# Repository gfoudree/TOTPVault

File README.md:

# TOTPVault

TOTPVault is a secure hardware vault for storing TOTP codes for two-factor authentication. It is compatible with websites and applications which support authenticators such as Google Authenticator or Authy.

TOTPVault uses an RISC-V ESP32-C3 microcontroller to perform cryptographic operations and storage/generation of TOTP codes with a separate chip to run an isolated USB stack.

## Demo

## Features

- Support for up to 64 credentials
- Cross platform, no drivers needed for Linux/MacOS
- Open source firmware, software, and hardware!

### Security Features (summary)
- TOTP secrets stored with AES256, decryption key derived from vault password via PBKDF2
- Trusted firmware via secure boot with attestation available
- ESP32-C3 HW RNG used for cryptographic operations
- USB stack isolated to separate chip to minimize attack surface
- Hardware locked down (JTAG disabled, eFuses set, etc)

# System Architecture
[System Architecture](https://gfoudree.github.io/TOTPVault/system-design/)

## Installation

First, clone the repository and build the `totpvault-cli` tool and build it:

```bash
git clone https://github.com/gfoudree/totpvault
cd totpvault/totpvault-cli
cargo build -r
```

The CLI program will be located at: `target/release/totpvault-cli`
## Documentation

[Documentation](https://gfoudree.github.io/TOTPVault/)

# FAQ

#### Why choose ESP32-C3 for the microcontroller?
The ESP32 chips have strong hardware security features such as HWRNG, encryption/hashing support, secure boot, and encrypted flash.

Other chips have some or all of these features, however the ESP32-C3 is [PSA-L1 certified](https://products.psacertified.org/products/esp32-c3-series/certificates#security-level-1), has good support for Rust firmware, and is affordable.

#### The ESP32 has Wifi/Bluetooth, does this device use either?
No, there is no antenna on the board and the Wifi/Bluetooth stack is disabled in the firmware.

#### If somebody steals my device, can they generate TOTP codes for my accounts?
No, as long as your password is strong they cannot unlock the vault and generate codes.

## Authors

- [@gfoudree](https://www.github.com/gfoudree)

## License

[GNU GPLv3](https://choosealicense.com/licenses/gpl-3.0/)

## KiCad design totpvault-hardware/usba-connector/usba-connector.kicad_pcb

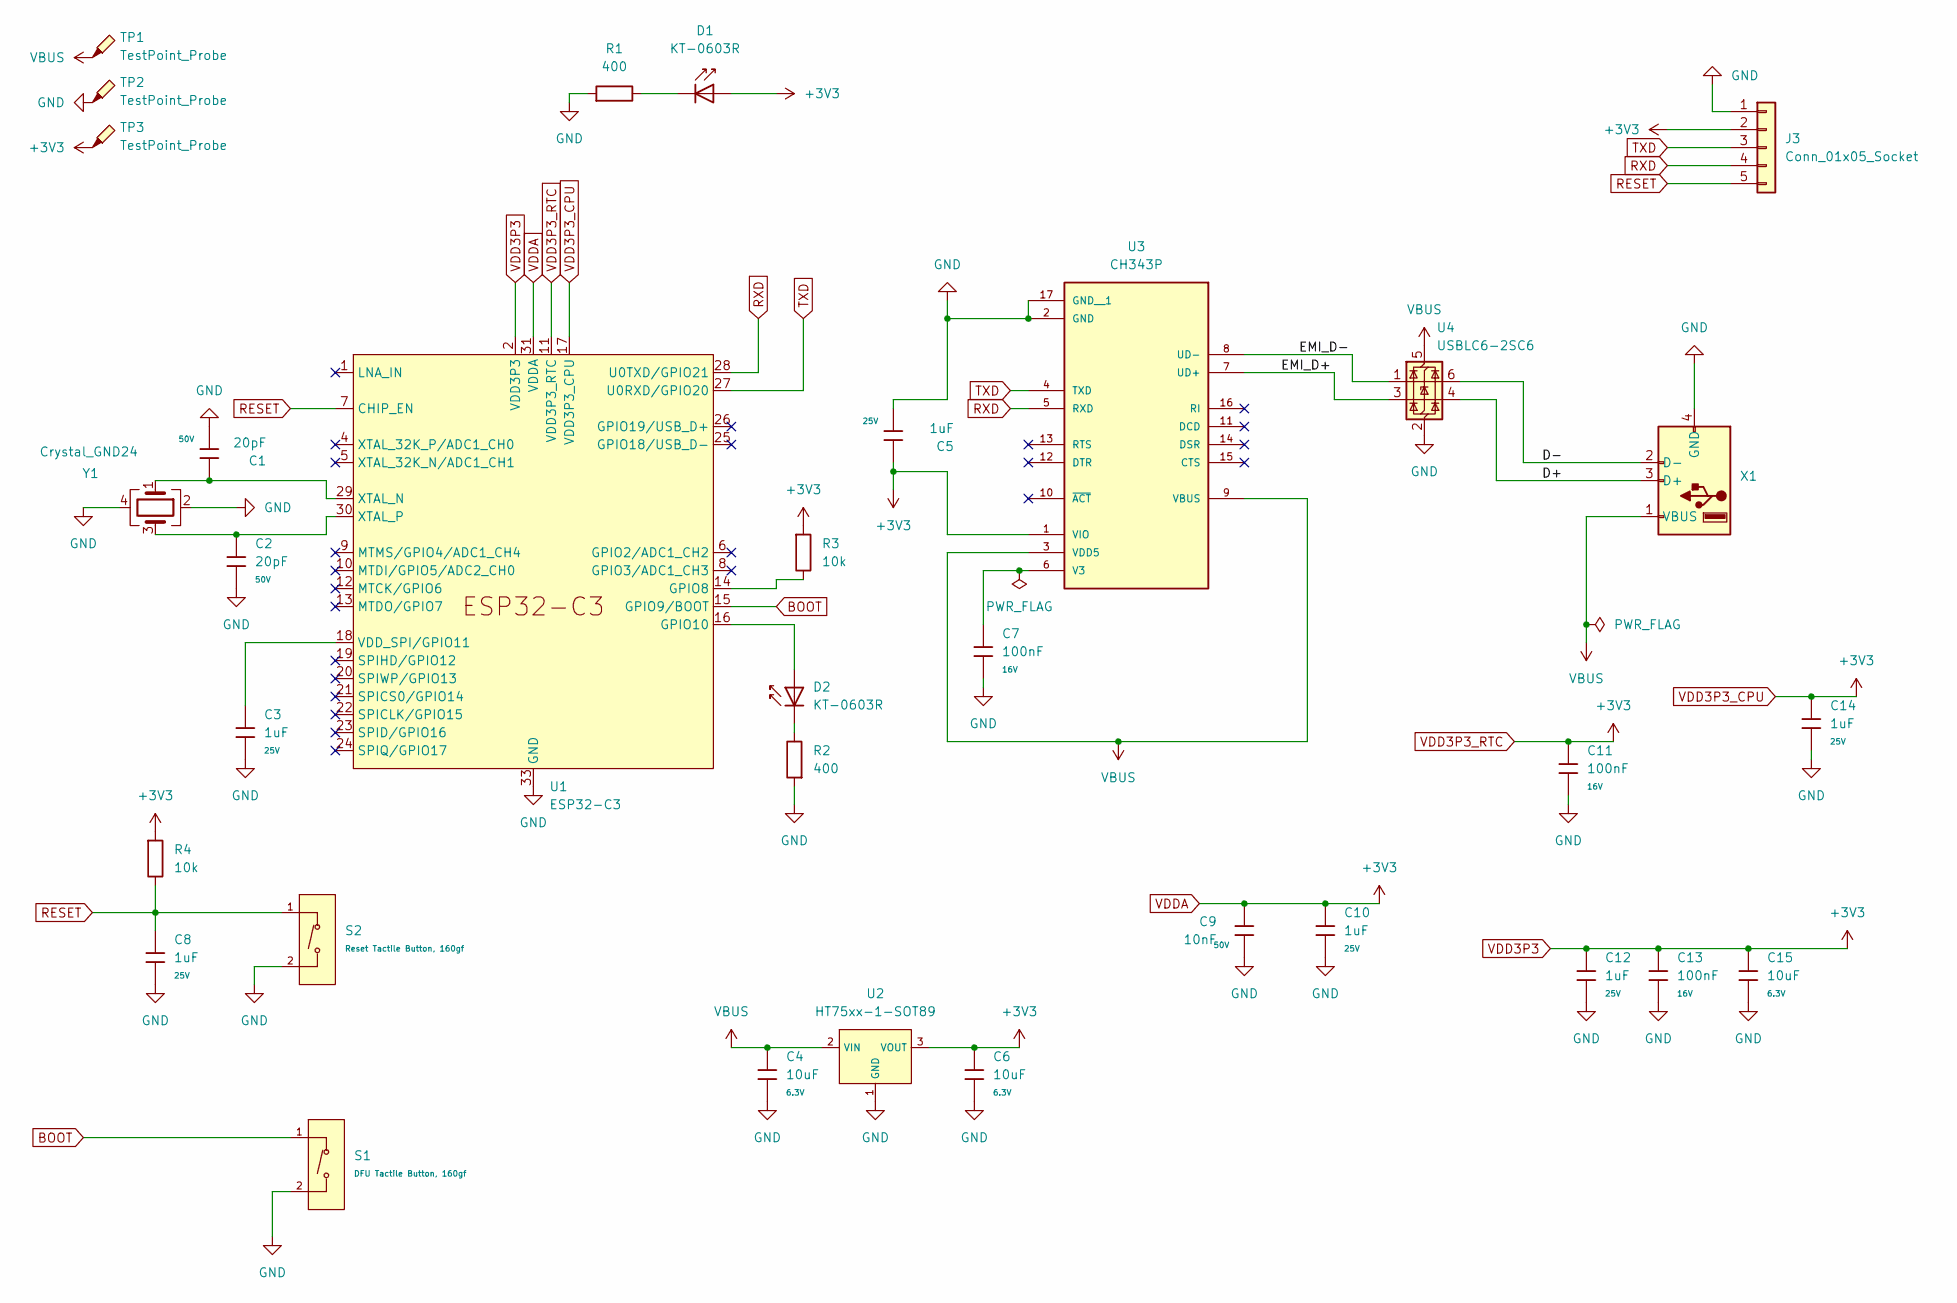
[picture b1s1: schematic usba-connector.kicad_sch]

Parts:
C1, C2: 20pF; C_0402; Voltage Rated 50V; Tolerance ±5%; Part 0402CG200J500NT; LCSC C1554
C3, C5, C8, C10, C12, C14: 1uF; C_0402; Voltage Rated 25V; Tolerance ±10%; Part CL05A105KA5NQNC; LCSC C52923
C4, C6, C15: 10uF; C_0402; Voltage Rated 6.3V; Tolerance ±20%; Part CL05A106MQ5NUNC; LCSC C15525
C7, C11, C13: 100nF; C_0402; Voltage Rated 16V; Tolerance ±10%; Part CL05B104KO5NNNC; LCSC C1525
C9: 10nF; C_0402; Voltage Rated 50V; Tolerance ±10%; Part CL05B103KB5NNNC; LCSC C15195
D1, D2: KT-0603R; D_0603; Part KT-0603R; LCSC C2286
J3: Conn_01x05_Socket; PinHeader_1x05_P2.54mm_Vertical
R1, R2: 400; R_0402; Overload Voltage (Max) 50V; Tolerance ±1%; Part 0402WGF1200TCE; LCSC C25079
R3, R4: 10k; R_0402; Overload Voltage (Max) 50V; Tolerance ±1%; Part 0402WGF1002TCE; LCSC C25744
S1: DFU Tactile Button, 160gf; SW_TS-1088-AR02016; Voltage Rating (Dc) 12V; Part TS-1088-AR02016; LCSC C720477
S2: Reset Tactile Button, 160gf; SW_TS-1088-AR02016; Voltage Rating (Dc) 12V; Part TS-1088-AR02016; LCSC C720477
TP1, TP2, TP3: TestPoint_Probe; TestPoint_Pad_D1.0mm
U1: ESP32-C3; QFN-32-1EP_5x5mm_P0.5mm_EP3.45x3.45mm
U2: HT75xx-1-SOT89; SOT-89-3_L4.5-W2.5-P1.50-LS4.2-BR; Output Voltage 3.3V; Dropout Voltage 55mV@(1mA); Part HT7533-1; LCSC C14289
U3: CH343P; PARTREV 1E
U4: USBLC6-2SC6; SOT-23-6
X1: USB_A_Molex_48037-2200_Horizontal
Y1: Crystal_GND24; Crystal_SMD_3225-4Pin_3.2x2.5mm

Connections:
/D+: U4.4 (I/O2), X1.3 (D+)
/D-: U4.6 (I/O1), X1.2 (D-)
/EMI_D+: U3.7 (UD+), U4.3 (I/O2)
/EMI_D-: U3.8 (UD-), U4.1 (I/O1)
BOOT: S1.1 (A), U1.15 (GPIO9/BOOT)
GND: C1.2, C2.2, C3.2, C4.2, C5.2, C6.2, C7.2, C8.2, C9.2, C10.2, C11.2, C12.2, C13.2, C14.2, C15.2, J3.1, R1.1, R2.1, S1.2 (B), S2.2 (B), TP2.1, U1.33 (GND), U2.1 (GND), U3.2 (GND), U3.17 (GND__1), U4.2 (GND), X1.4 (GND), Y1.2, Y1.4
unnamed: D1.1, R1.2
unnamed: D2.1, R2.2
unnamed: R3.2, U1.14 (GPIO8)
unnamed: D2.2, U1.16 (GPIO10)
unnamed: C3.1, U1.18 (VDD_SPI/GPIO11)
unnamed: C1.1, U1.29 (XTAL_N), Y1.1
unnamed: C2.1, U1.30 (XTAL_P), Y1.3
unnamed: C7.1, U3.6 (V3)
RESET: C8.1, J3.5, R4.2, S2.1 (A), U1.7 (CHIP_EN)
RXD: J3.4, U1.28 (U0TXD/GPIO21), U3.5 (RXD)
TXD: J3.3, U1.27 (U0RXD/GPIO20), U3.4 (TXD)
VBUS: C4.1, TP1.1, U2.2 (VIN), U3.3 (VDD5), U3.9 (VBUS), U4.5 (VBUS), X1.1 (VBUS)
VDD3P3: C5.1, C6.1, C9.1, C10.1, C11.1, C12.1, C13.1, C14.1, C15.1, D1.2, J3.2, R3.1, R4.1, TP3.1, U1.2 (VDD3P3), U1.3 (VDD3P3), U1.11 (VDD3P3_RTC), U1.17 (VDD3P3_CPU), U1.31 (VDDA), U1.32 (VDDA), U2.3 (VOUT), U3.1 (VIO)

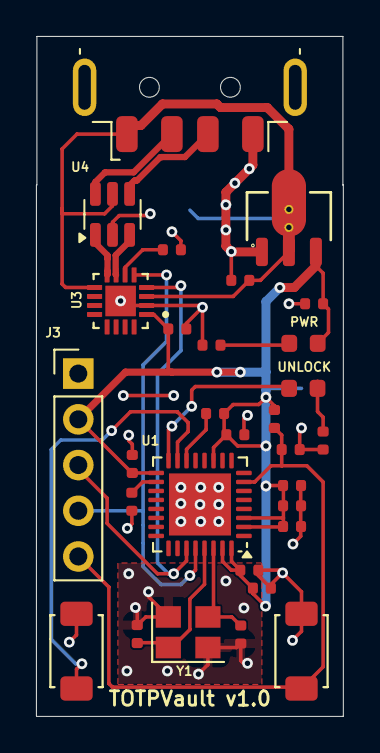
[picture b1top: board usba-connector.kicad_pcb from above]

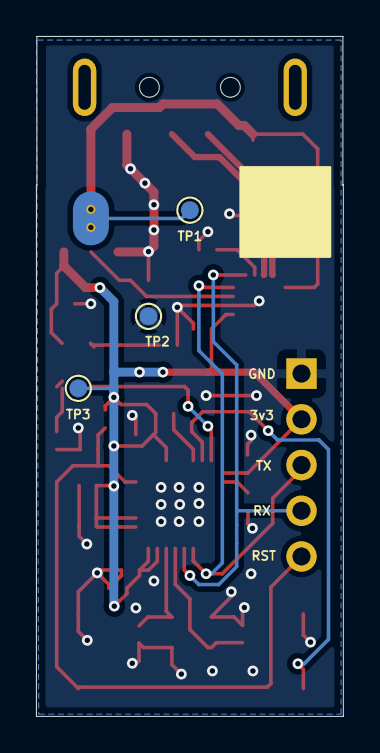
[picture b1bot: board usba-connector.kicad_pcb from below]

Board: 2 copper layers, 17.1 x 37.8 mm, 33 parts (3 on the bottom side), 19 nets.

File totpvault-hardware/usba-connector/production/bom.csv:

Designator,Footprint,Quantity,Value,LCSC Part #
"C1, C2",0402,2,20pF,
"C10, C12, C14, C3, C5, C8",0402,6,1uF,
"C11, C13, C7",0402,3,100nF,
"C15, C4, C6",0402,3,10uF,
C9,0402,1,10nF,
D1,0603,1,KT-0603R,
J3,PinHeader_1x06_P2.54mm_Vertical,1,Conn_01x06_Socket,
R1,0402,1,100,
R2,0402,1,499,
"R3, R4",0402,2,10k,
"TP1, TP2, TP3",TestPoint_Pad_D1.0mm,3,TestPoint_Probe,
U1,QFN-32-1EP_5x5mm_P0.5mm_EP3.45x3.45mm,1,ESP32-C3,
U2,SOT-89-3,1,HT75xx-1-SOT89,
U3,CH343P,1,CH343P,
U4,SOT-23-6,1,USBLC6-2SC6,
X1,USB_A_Molex_48037-2200_Horizontal,1,~,
Y1,Crystal_SMD_3225-4Pin_3.2x2.5mm,1,Crystal_GND24,

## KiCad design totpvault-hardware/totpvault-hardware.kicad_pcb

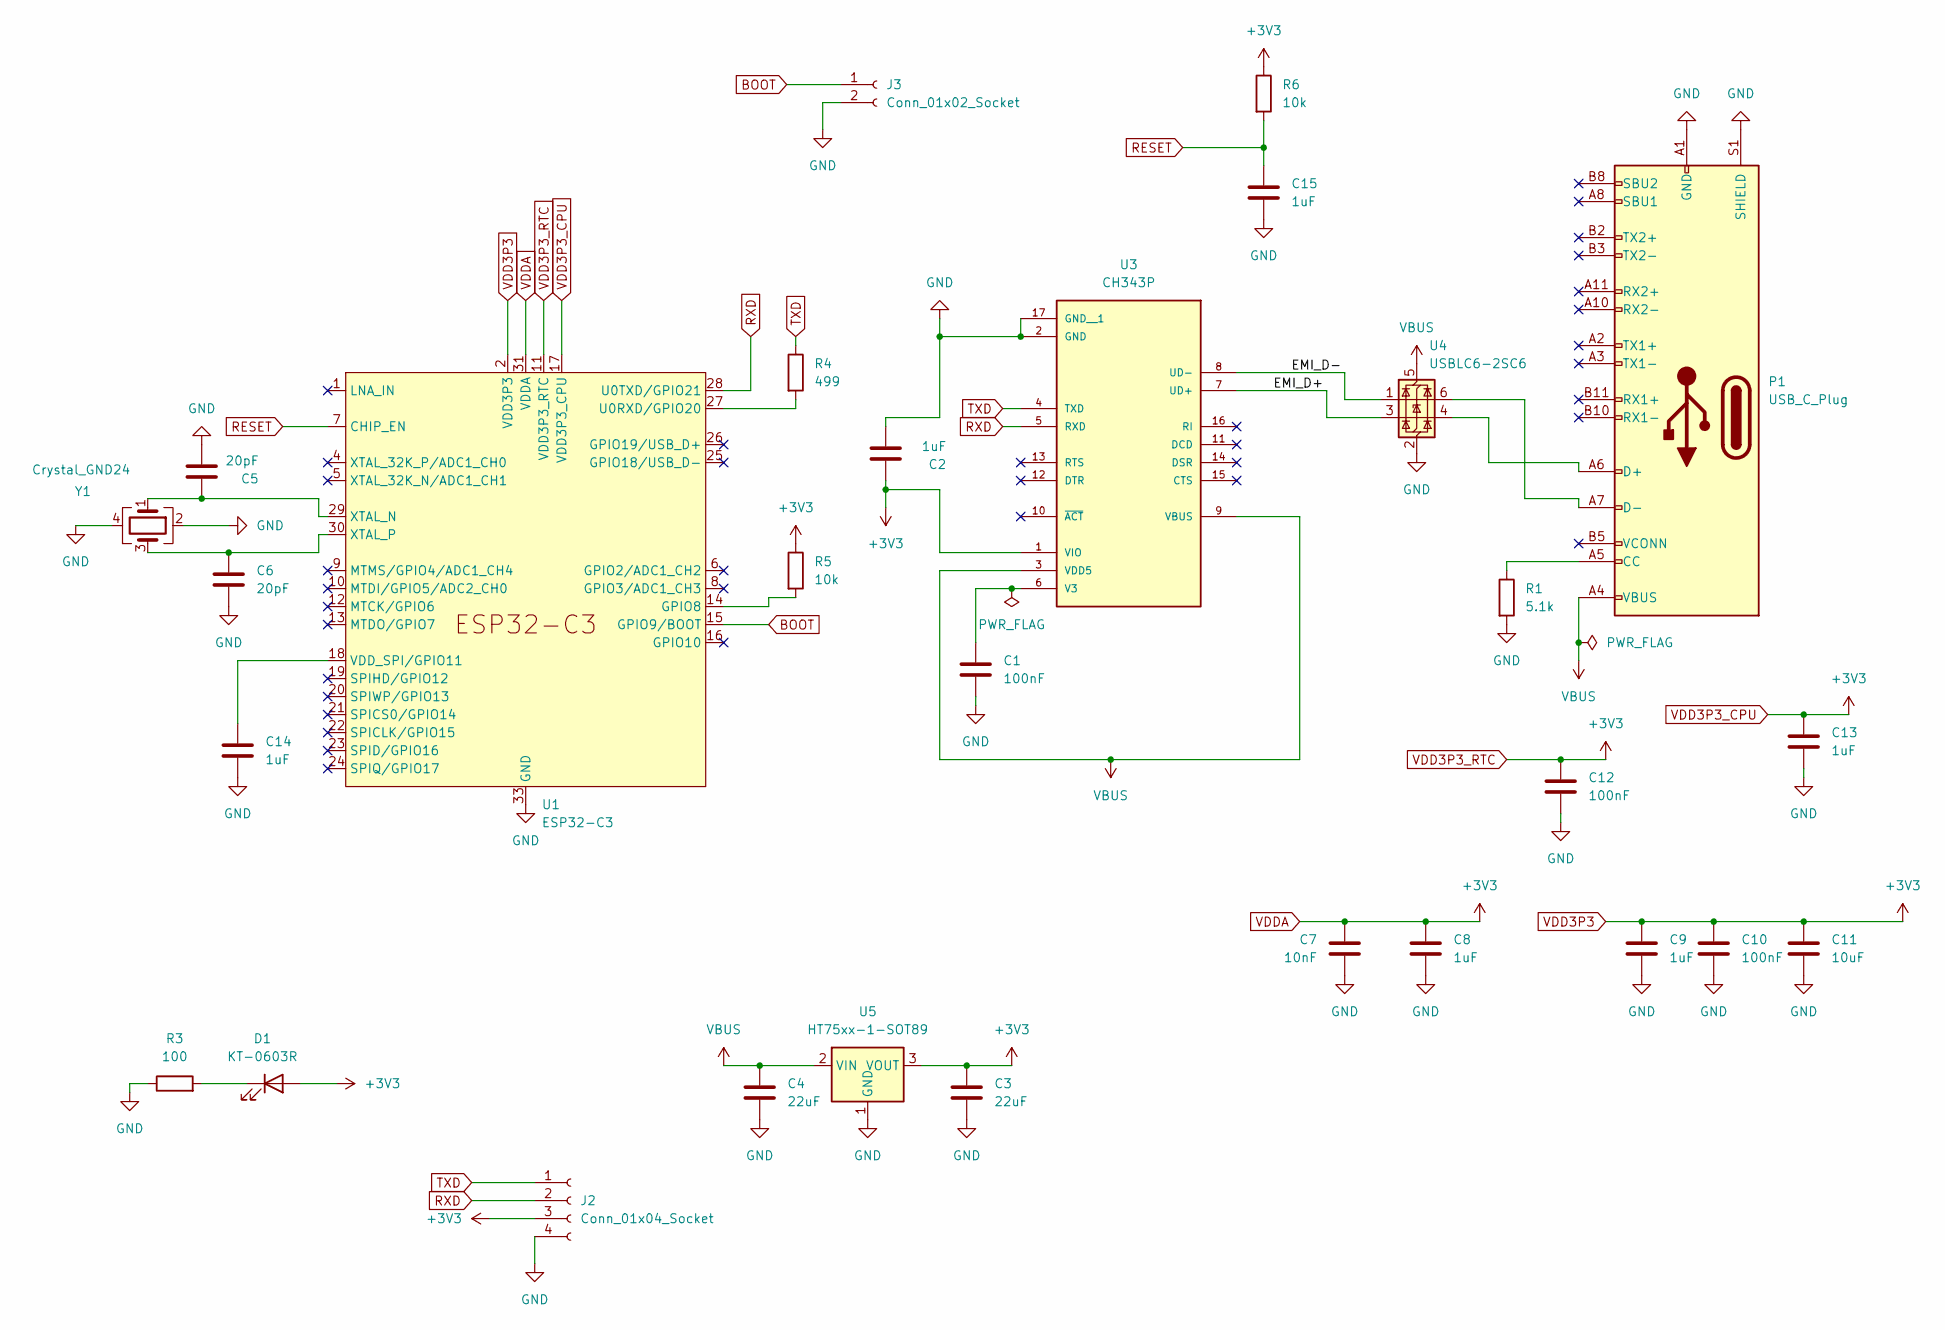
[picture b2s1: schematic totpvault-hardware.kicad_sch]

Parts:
C1, C10, C12: 100nF; C_0603_1608Metric
C2, C8, C9, C13, C14, C15: 1uF; C_0603_1608Metric
C3, C4: 22uF; C_0603_1608Metric
C5, C6: 20pF; C_0402_1005Metric
C7: 10nF; C_0603_1608Metric
C11: 10uF; C_0603_1608Metric
D1: KT-0603R; LED_0603_1608Metric
J2: Conn_01x04_Socket; PinHeader_1x04_P2.54mm_Vertical
J3: Conn_01x02_Socket; PinHeader_1x02_P2.54mm_Vertical
P1: USB_C_Plug; USB_C_Plug_Molex_105444
R1: 5.1k; R_0603_1608Metric
R3: 100; R_0603_1608Metric
R4: 499; R_0603_1608Metric
R5, R6: 10k; R_0603_1608Metric
U1: ESP32-C3; QFN-32-1EP_5x5mm_P0.5mm_EP3.45x3.45mm
U3: CH343P; PARTREV 1E
U4: USBLC6-2SC6; SOT-23-6
U5: HT75xx-1-SOT89; SOT-89-3
Y1: Crystal_GND24; Crystal_SMD_3225-4Pin_3.2x2.5mm

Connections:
/EMI_D+: U3.7 (UD+), U4.3 (I/O2)
/EMI_D-: U3.8 (UD-), U4.1 (I/O1)
BOOT: J3.1, U1.15 (GPIO9/BOOT)
GND: C1.2, C2.2, C3.2, C4.2, C5.2, C6.2, C7.2, C8.2, C9.2, C10.2, C11.2, C12.2, C13.2, C14.2, C15.2, J2.4, J3.2, P1.A1 (GND), P1.A12 (GND), P1.B1 (GND), P1.B12 (GND), P1.S1 (SHIELD), R1.2, R3.1, U1.33 (GND), U3.2 (GND), U3.17 (GND__1), U4.2 (GND), U5.1 (GND), Y1.2, Y1.4
unnamed: D1.1 (K), R3.2
unnamed: P1.A5 (CC), R1.1
unnamed: P1.A6 (D+), U4.4 (I/O2)
unnamed: P1.A7 (D-), U4.6 (I/O1)
unnamed: R5.2, U1.14 (GPIO8)
unnamed: R4.2, U1.27 (U0RXD/GPIO20)
unnamed: C14.1, U1.18 (VDD_SPI/GPIO11)
unnamed: C5.1, U1.29 (XTAL_N), Y1.1
unnamed: C6.1, U1.30 (XTAL_P), Y1.3
unnamed: C1.1, U3.6 (V3)
RESET: C15.1, R6.2, U1.7 (CHIP_EN)
RXD: J2.2, U1.28 (U0TXD/GPIO21), U3.5 (RXD)
TXD: J2.1, R4.1, U3.4 (TXD)
VBUS: C4.1, P1.A4 (VBUS), P1.A9 (VBUS), P1.B4 (VBUS), P1.B9 (VBUS), U3.3 (VDD5), U3.9 (VBUS), U4.5 (VBUS), U5.2 (VIN)
VDD3P3: C2.1, C3.1, C7.1, C8.1, C9.1, C10.1, C11.1, C12.1, C13.1, D1.2 (A), J2.3, R5.1, R6.1, U1.2 (VDD3P3), U1.3 (VDD3P3), U1.11 (VDD3P3_RTC), U1.17 (VDD3P3_CPU), U1.31 (VDDA), U1.32 (VDDA), U3.1 (VIO), U5.3 (VOUT)

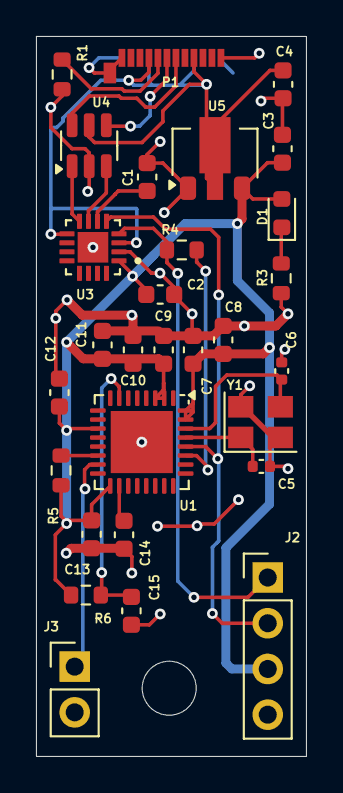
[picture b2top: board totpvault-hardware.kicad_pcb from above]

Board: 2 copper layers, 15.0 x 40.0 mm, 29 parts (0 on the bottom side), 19 nets.

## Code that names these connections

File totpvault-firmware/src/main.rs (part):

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use critical_section::Mutex;
use crypto::{gen_ed25519_keypair, gen_salt, get_ed25519_public_key_nvs, sign_challenge};
use ed25519_dalek::SECRET_KEY_LENGTH;
use esp_idf_svc::hal::gpio::{Gpio10, InterruptType, Output, PinDriver, Pull};
use esp_idf_svc::hal::timer::{TimerConfig, TimerDriver};
use esp_idf_svc::nvs::{EspDefaultNvsPartition, EspNvsPartition, NvsDefault};
use esp_idf_svc::{
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        &mut self,
        cmd_buf: &[u8; 512],
        read_bytes: usize,
        unlocked_led: &mut PinDriver<Gpio10, Output>,
    ) -> Result<(), String> {
        let unlock_msg = rmp_serde::from_slice::<UnlockMsg>(&cmd_buf[1..read_bytes])
            .map_err(|_| "Invalid Unlock message".to_string())?;
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        self.key = key;
        critical_section::with(|cs| VAULT_STATUS_UNLOCKED.borrow(cs).set(true));

        // Set board LED GPIO10 to on for unlocked
        unlocked_led.set_high().unwrap();

        // Reset auth counter
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        .flow_control(uart::config::FlowControl::None);

    // Setup status LED and lock button
    let mut unlocked_led = PinDriver::output(peripherals.pins.gpio10).unwrap();
    unlocked_led.set_low().unwrap();
    let mut lock_button = PinDriver::input(peripherals.pins.gpio9).unwrap();
    lock_button.set_pull(Pull::Up).unwrap(); // Pull "BOOT" button up
    lock_button
        .set_interrupt_type(InterruptType::PosEdge)
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    // After this line, logging stops working as UART is taken over for host <-> dev communication
    let mut uart: uart::UartDriver = uart::UartDriver::new(
        peripherals.uart1,
        peripherals.pins.gpio21,
        peripherals.pins.gpio20,
        Option::<AnyIOPin>::None,
        Option::<AnyIOPin>::None,
        &config,
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
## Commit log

2024-10-18 First commit, firmware working
2024-10-21 Added vault lock and unit tests for attestation
2024-10-21 TOTP working! Unit test written to validate
2024-10-24 Refactoring code to use messagepack for all communication
2024-10-24 Refactoring message structures, bug fixed with serializing attestation where LF and NL characters broke over serial
2024-10-25 Code cleanup, migration to msgpack only API
2024-11-20 Fixed issue with toolchain, compiling again
2024-11-26 Cleaned up status message
2024-11-26 Major restructuring
2024-12-19 PCB reworking, added labels to GUI
2024-12-28 PCB order
2024-12-30 Serial port communication with device working with GUI now
2025-01-12 Countdown timer on GUI working
2025-01-15 Filled out UI for configuring the key
2025-01-20 Porting to MacOS. Bug with public key from device being truncated to 24 bytes instead of 32
2025-01-21 Bugfix for serial port comm, needed to flush boot messages from buffer on first boot
2025-01-24 Code cleanup, displaying timesync status and fingerprint
2025-01-25 Code cleanup, added some template functions for device
2025-01-26 Refactoring code to use signals. Time sync working with device
2025-01-31 Added initialize vault button
2025-02-02 Added helper function for communicating with the device
2025-02-05 Added zeroize to sensitive fields, code cleanup
2025-02-07 Updated disabled widgets for when device is unplugged
2025-02-11 Updating firmware to use less .unwrap() calls
2025-02-11 Code cleanup
2025-02-11 Shifting to a CLI for faster development
2025-02-11 Added more commands
2025-02-11 Added more CLI functions, moved sync-time function behind vault unlock. Firmware build broken on Linux
2025-02-11 Added CLI init command
2025-02-12 FW builds working again, serialport and nix library conflicting versions. Split code
2025-02-12 Builds working again
2025-02-14 Refactoring totpvault comm code
2025-02-15 Implemented add and list
2025-02-15 Attestation working
2025-02-16 Code cleanup, removed some warnings
2025-02-16 Added some testcases, fixed some bugs
2025-02-19 Forking to create USB-A connector device
2025-02-20 Added more testcases, fixed some bugs. Currently, adding many entries corrupts the database
2025-02-20 Finalized USB-A PCB
2025-02-20 Order ready for USB-A
2025-03-05 Modified USB-A connector to use a physical connector instead of PCB slice due to pricing of ordering 2mm gold-plated PCBs
2025-03-06 Added silkscreen for barcode on PCB order
2025-03-11 Fixed 2 major bugs, one with the toolchain being too new causing panics, the other with not waiting for esp32 responses over UART
2025-03-11 ESP IDF 5.2.3 is working SDK
2025-03-11 Adding test cases to test TOTP code generation
2025-03-12 Added LTO and code optimization to release builds, not tested
2025-03-12 Code cleanup, added time-sync checks and cleaned formatting for listing credentials
2025-03-12 Added variable delays for device as 1.5s delay skews TOTP codes and not all commands need this much time
2025-03-13 Refactored TOTP code test to allow 1s code mismatches. Added readme
2025-03-13 Added attestation unit tests and fixed max value in firmware
2025-03-16 Added stack-smashing protection to RTOS
2025-03-25 Finalized PCB, added label and fixed solder mask
2025-03-26 Added logging to firmware boot, configured larger NVS partition but espflash does not work properly
2025-03-26 Bugfix, esp32-c3 uses different GPIO pins for TX/RX UART
2025-03-29 Added documentation
2025-03-31 Updated documentation, refactored some code
2025-04-01 Bugfix for Gmail
2025-04-03 Added script to help with code signing, small code cleanup
2025-04-03 Secure boot and flash encryption enabled
2025-04-04 Updated compiler version and dependencies
2025-04-04 Fixed bug where device was wiping NVS on each boot
2025-04-09 Updated documentation, added manual timeout option to CLI
2025-12-24 Finalized new board design with JLCPCB basic parts, code cleanup
2026-01-10 Updated documentation with schematics and images, delete GUI project, PCB 3D design cleanup
2026-01-12 Added config settings to the firmware
2026-01-15 Added demo gif and additional documentation
2026-01-15 Deployed ca146d8 with MkDocs version: 1.6.1
2026-01-15 Fixed links, added GPLv3
2026-01-15 Deployed 32899b2 with MkDocs version: 1.6.1
2026-01-15 Fixed one more link
2026-01-15 Deployed 5be7c44 with MkDocs version: 1.6.1
2026-02-18 Added vault auto-lock feature, migrated management script to a Justfile
2026-02-19 Refactored storage API to be more correct
2026-02-24 Fixed bug on first device init where NVS handle became invalid after formatting NVS
2026-03-04 Code cleanup, added some additional security to zeroize keys after vault lock via button
2026-05-17 Migrated to Argon2id for KDF, fixed potential panics, added additional zeroize of regions, code formatting cleanup
2026-05-17 Added login rate limiting
2026-06-18 Fixed issue with Argon2 hashing using too much memory
2026-06-18 Code formatting, increased timeout for UART for QEMU
2026-06-19 Moved UART protocol to use length field instead of waits
2026-06-20 1.0 stable release. Added unit test for autolock and set it to take effect after changing the setting
2026-06-20 Deployed 70a8f50 with MkDocs version: 1.6.1
2026-06-21 Update docs with additional commands
2026-06-21 Deployed 6f67e0e with MkDocs version: 1.6.1
2026-06-21 Code cleanup and version update
